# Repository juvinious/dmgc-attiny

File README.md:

# DMGC-ATTINY VIEWER

A software implementation of the ATTINY85 code that [BucketM0use](https://github.com/MouseBiteLabs/) made for the [DMGC](https://github.com/MouseBiteLabs/Game-Boy-DMG-Color).

# HOW TO USE

## Run with SDL2

- Install c++ development tools, libyaml-cpp and SDL2
  - Example in Ubuntu install: apt-get install build-essential libyaml-cpp-dev libsdl2-dev 
- make
- executables are dropped in bin directory

## Examples

There are currently three example sketches

### DMGC-IPS-ATTINY85

This is the original sketch. Refer to [DMGC-IPS-01](https://github.com/MouseBiteLabs/Game-Boy-DMG-Color/tree/main/DMGC-IPS-01#button-leds-and-attiny85) for details.

### DMGC-IPS-ATTINY85-PLUS

This is the same as the original, but improved using the key/button handler which is using states to determine the positions of buttons. Better practice instead of blocking with while loops. :P.

### BREATHING

A more extended example, allowing for different modes.
  - Breathing - Increases and decreases brightness at a specific rate. Changes to random color when brightness is at 5 or below, starting a new cycle
  - Left to Right (LTR) - Run a gradient from left to right while brightning the a random color to the max, fade out and then restart
  - Right to Left - Same as LTR, but going in the opposite direction
  - Center Out - Same as LTR, but starting from right and select and going outward
  - Out to Center - Same as LTR, but starting at up and A
  - Random - Randomizes the order of the cycling as LTR

## Deploy to ATTINY85 in Arduino IDE

- Symlink library directory as src in the directory of the sketch
  - In windows: mklink /J src ..\..\library
  - In linux: ln -s ../../library src
- Open ino sketch, compile & upload

## Finally

Have fun!

# TODO

- Cleanup/Optimize configuration content
- Add additional utils as needed
- Adafruit_NeoPixel
  - Implement other functionality
- EEPROM
  - Fix get/put templating
  - Implement other functionality
- Implement fast_led library functionality (http://fastled.io/)
- Try to match as close as possible the hardware speed at 8mhz

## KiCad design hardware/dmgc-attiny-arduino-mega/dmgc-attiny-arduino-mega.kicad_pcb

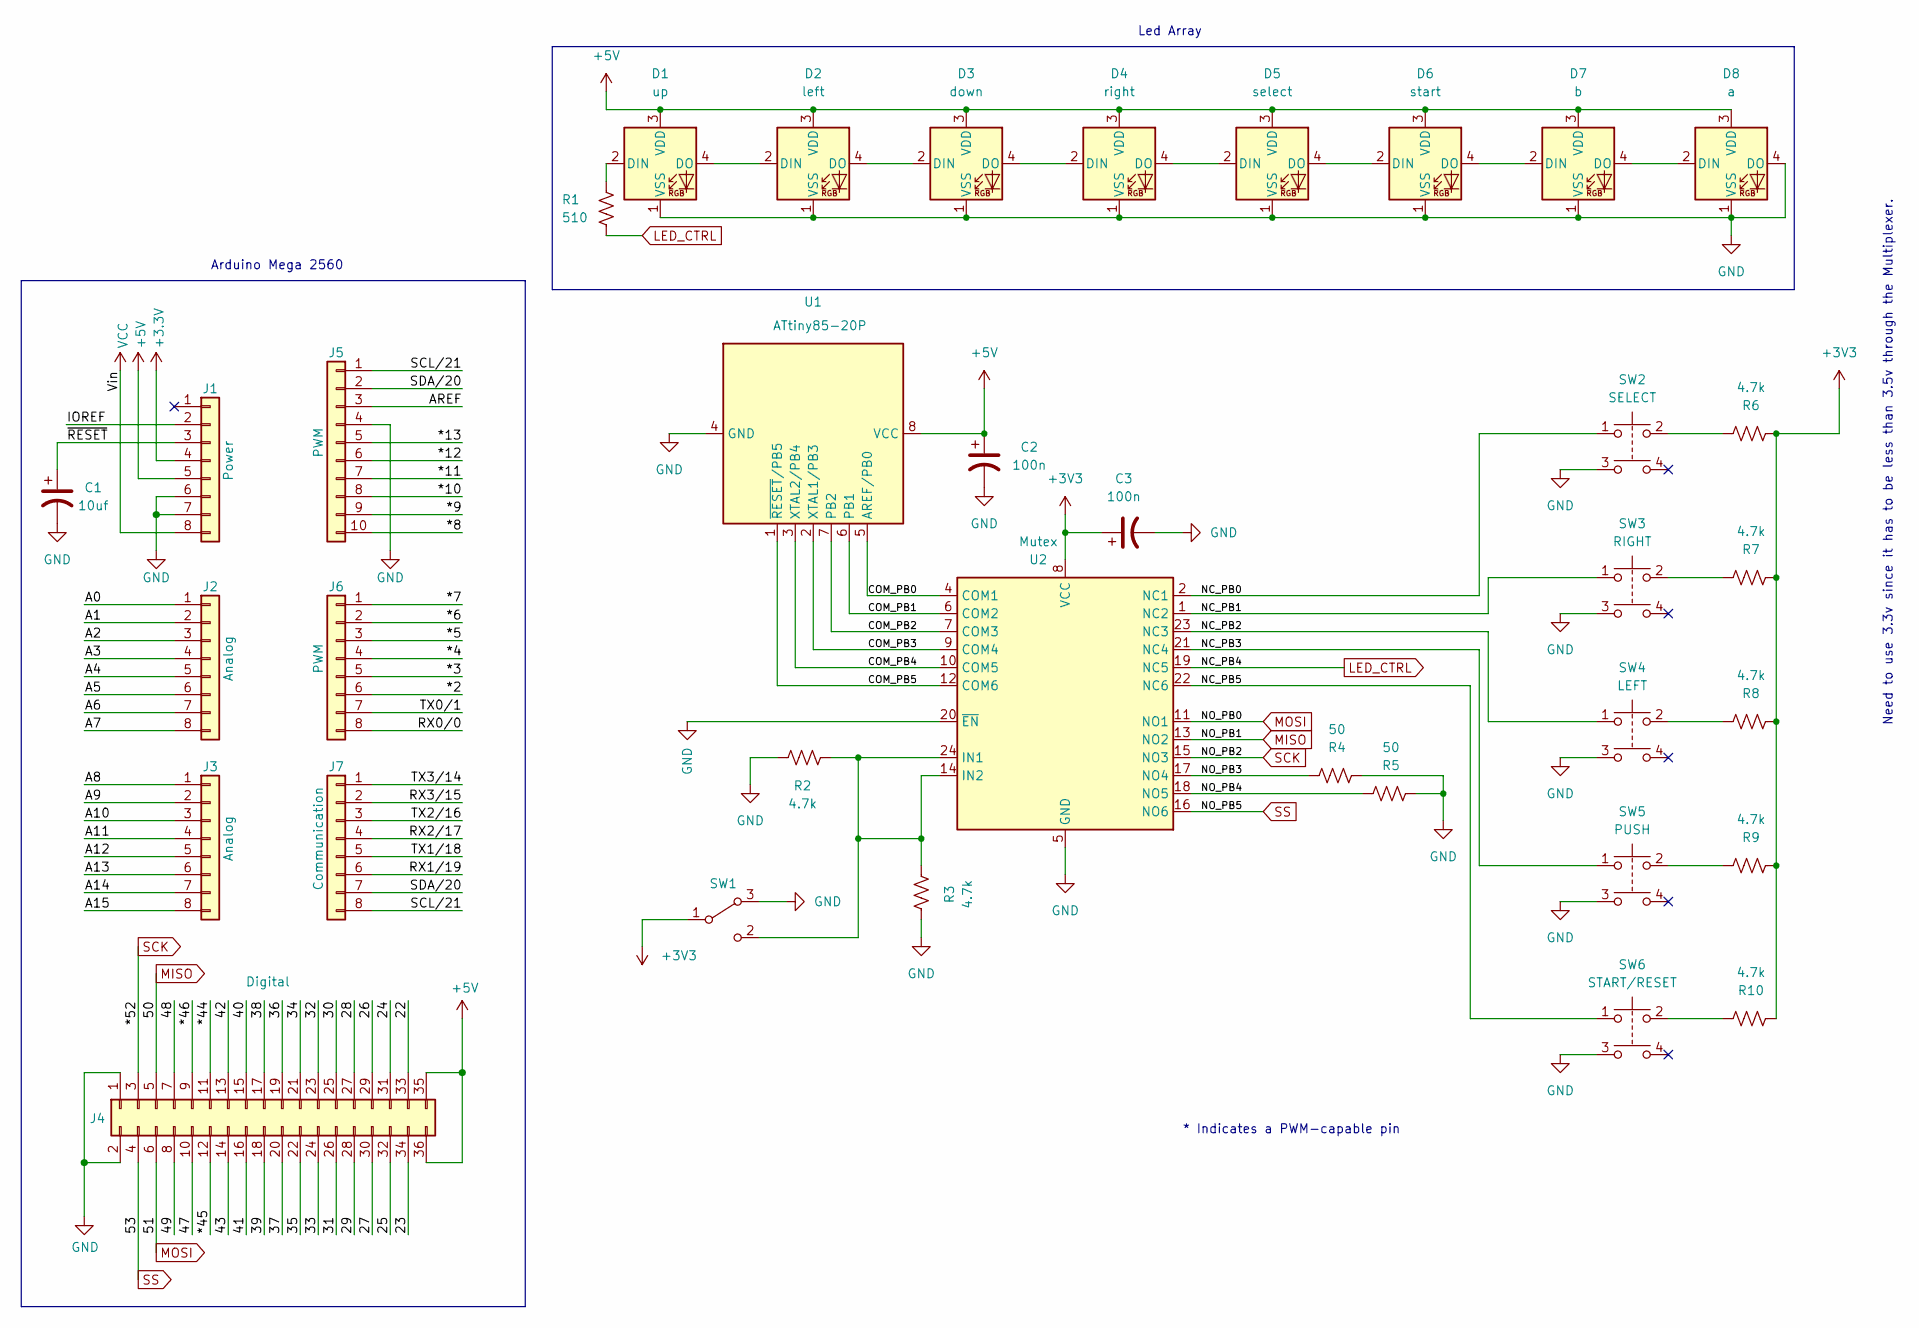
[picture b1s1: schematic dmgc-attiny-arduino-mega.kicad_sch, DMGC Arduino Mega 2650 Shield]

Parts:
C1: 10uf; C_0603_1608Metric
C2, C3: 100n; C_0603_1608Metric
D1: up; LED_Inolux_IN-PI554FCH_PLCC4_5.0x5.0mm_P3.2mm
D2: left; LED_Inolux_IN-PI554FCH_PLCC4_5.0x5.0mm_P3.2mm
D3: down; LED_Inolux_IN-PI554FCH_PLCC4_5.0x5.0mm_P3.2mm
D4: right; LED_Inolux_IN-PI554FCH_PLCC4_5.0x5.0mm_P3.2mm
D5: select; LED_Inolux_IN-PI554FCH_PLCC4_5.0x5.0mm_P3.2mm
D6: start; LED_Inolux_IN-PI554FCH_PLCC4_5.0x5.0mm_P3.2mm
D7: b; LED_Inolux_IN-PI554FCH_PLCC4_5.0x5.0mm_P3.2mm
D8: a; LED_Inolux_IN-PI554FCH_PLCC4_5.0x5.0mm_P3.2mm
J1: Power; PinSocket_1x08_P2.54mm_Vertical
J2, J3: Analog; PinSocket_1x08_P2.54mm_Vertical
J4: Digital; PinSocket_2x18_P2.54mm_Vertical
J5: PWM; PinSocket_1x10_P2.54mm_Vertical
J6: PWM; PinSocket_1x08_P2.54mm_Vertical
J7: Communication; PinSocket_1x08_P2.54mm_Vertical
R1: 510; R_0603_1608Metric
R2, R3, R6, R7, R8, R9, R10: 4.7k; R_0603_1608Metric
R4, R5: 50; R_0603_1608Metric
SW1: Toggle Flash / Run; SW_E-Switch_EG1224_SPDT_Angled
SW2: SELECT; SW_PUSH_6mm
SW3: RIGHT; SW_PUSH_6mm
SW4: LEFT; SW_PUSH_6mm
SW5: PUSH; SW_PUSH_6mm
SW6: START/RESET; SW_PUSH_6mm
U1: ATtiny85-20P; DIP-8_W7.62mm
U2: Mutex; TSSOP-24_4.4x7.8mm_P0.65mm

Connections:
+5V: C2.1, D1.3 (VDD), D2.3 (VDD), D3.3 (VDD), D4.3 (VDD), D5.3 (VDD), D6.3 (VDD), D7.3 (VDD), D8.3 (VDD), J1.5, J4.35, J4.36, U1.8 (VCC)
/22: J4.33
/23: J4.34
/24: J4.31
/25: J4.32
/26: J4.29
/27: J4.30
/28: J4.27
/29: J4.28
/30: J4.25
/31: J4.26
/32: J4.23
/33: J4.24
/34: J4.21
/35: J4.22
/36: J4.19
/37: J4.20
/38: J4.17
/39: J4.18
/40: J4.15
/41: J4.16
/42: J4.13
/43: J4.14
/47: J4.10
/48: J4.7
/49: J4.8
/*2: J6.6
/*3: J6.5
/*4: J6.4
/*5: J6.3
/*6: J6.2
/*7: J6.1
/*8: J5.10
/*9: J5.9
/*10: J5.8
/*11: J5.7
/*12: J5.6
/*13: J5.5
/*44: J4.11
/*45: J4.12
/*46: J4.9
/A0: J2.1
/A1: J2.2
/A2: J2.3
/A3: J2.4
/A4: J2.5
/A5: J2.6
/A6: J2.7
/A7: J2.8
/A8: J3.1
/A9: J3.2
/A10: J3.3
/A11: J3.4
/A12: J3.5
/A13: J3.6
/A14: J3.7
/A15: J3.8
/AREF: J5.3
/COM_PB0: U1.5 (AREF/PB0), U2.4 (COM1)
/COM_PB1: U1.6 (PB1), U2.6 (COM2)
/COM_PB2: U1.7 (PB2), U2.7 (COM3)
/COM_PB3: U1.2 (XTAL1/PB3), U2.9 (COM4)
/COM_PB4: U1.3 (XTAL2/PB4), U2.10 (COM5)
/COM_PB5: U1.1 (~RESET/PB5), U2.12 (COM6)
/IOREF: J1.2
/NC_PB0: SW2.1, U2.2 (NC1)
/NC_PB1: SW3.1, U2.1 (NC2)
/NC_PB2: SW4.1, U2.23 (NC3)
/NC_PB3: SW5.1, U2.21 (NC4)
/NC_PB5: SW6.1, U2.22 (NC6)
/NO_PB3: R4.2, U2.17 (NO4)
/NO_PB4: R5.2, U2.18 (NO5)
/RX0/0: J6.8
/RX1/19: J7.6
/RX2/17: J7.4
/RX3/15: J7.2
/SCL/21: J5.1, J7.8
/SDA/20: J5.2, J7.7
/TX0/1: J6.7
/TX1/18: J7.5
/TX2/16: J7.3
/TX3/14: J7.1
/~RESET: C1.1, J1.3
GND: C1.2, C2.2, C3.2, D1.1 (VSS), D2.1 (VSS), D3.1 (VSS), D4.1 (VSS), D5.1 (VSS), D6.1 (VSS), D7.1 (VSS), D8.1 (VSS), D8.4 (DO), J1.6, J1.7, J4.1, J4.2, J5.4, R2.1, R3.1, R4.1, R5.1, SW1.3 (A), SW2.3, SW3.3, SW4.3, SW5.3, SW6.3, U1.4 (GND), U2.5 (GND), U2.20 (~EN)
LED_CTRL: R1.1, U2.19 (NC5)
MISO: J4.5, U2.13 (NO2)
MOSI: J4.6, U2.11 (NO1)
unnamed: D1.2 (DIN), R1.2
unnamed: D1.4 (DO), D2.2 (DIN)
unnamed: D2.4 (DO), D3.2 (DIN)
unnamed: D3.4 (DO), D4.2 (DIN)
unnamed: D4.4 (DO), D5.2 (DIN)
unnamed: D5.4 (DO), D6.2 (DIN)
unnamed: D6.4 (DO), D7.2 (DIN)
unnamed: D7.4 (DO), D8.2 (DIN)
unnamed: R2.2, R3.2, SW1.2 (C), U2.14 (IN2), U2.24 (IN1)
unnamed: R6.2, SW2.2
unnamed: R7.2, SW3.2
unnamed: R8.2, SW4.2
unnamed: R9.2, SW5.2
unnamed: R10.2, SW6.2
SCK: J4.3, U2.15 (NO3)
SS: J4.4, U2.16 (NO6)
VCC: J1.8

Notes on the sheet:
Need to use 3.3v since it has to be less than 3.5v through the Multiplexer.
Arduino Mega 2560
Led Array
* Indicates a PWM-capable pin

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
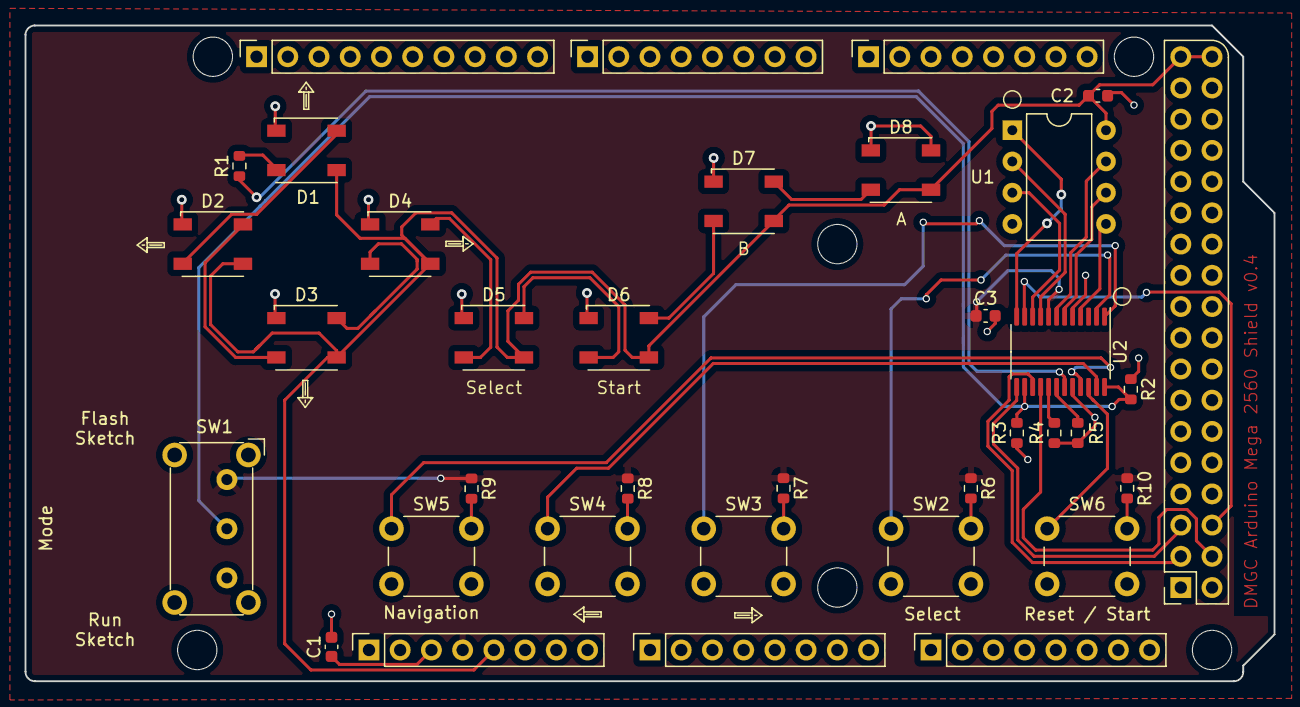
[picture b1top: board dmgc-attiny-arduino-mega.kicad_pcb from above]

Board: 2 copper layers, 101.6 x 53.3 mm, 48 parts (0 on the bottom side), 38 nets.

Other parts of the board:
MH1, MH2, MH3, MH4, MH5, MH6: MountingHole_3.2mm
arrow**: Up; Arrow
arrow**#2, arrow**#4, arrow**#6: Left; Arrow
arrow**#3: Down; Arrow
arrow**#5: Right; Arrow

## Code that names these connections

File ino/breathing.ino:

#include <Adafruit_NeoPixel.h>
#include <EEPROM.h>

// Which pin on the Arduino is connected to the NeoPixels?
#define OUT           PCINT4 // PB4
#define pushbtn       PCINT3 // PB3
#define leftbtn       PCINT2 // PB2
#define rightbtn      PCINT1 // PB1
#define selbtn        PCINT0 // PB0

// Define order of LEDs in string, starting with 0
#define l             1
#define u             0
#define d             2
#define r             3
#define se            4
#define st            5
#define b             6
#define a             7

#define NUMPIXELS 8 // Popular NeoPixel ring size

Adafruit_NeoPixel pixels(NUMPIXELS, OUT, NEO_GRB + NEO_KHZ800);

volatile uint8_t brightness;
volatile uint8_t color_type;
const uint8_t    COLOR_QTY  = 9;
const uint8_t    DEBOUNCE_DELAY = 50;
const uint8_t    BRIGHTNESS_INC = 5;
const uint8_t    MIN_BRIGHTNESS = 5;
const uint8_t    MAX_BRIGHTNESS = 50;

volatile uint8_t brightness_change_flag = 0;

// cycles through different colors:    red  org  ylw  grn  cyan blue purp wht  off
volatile uint8_t red[COLOR_QTY]   =  { 255, 255, 255, 0,   0,   0,   255, 255, 0};
volatile uint8_t green[COLOR_QTY] =  { 0,   100, 200, 255, 255, 0,   0,   255, 0};
volatile uint8_t blue[COLOR_QTY]  =  { 0,   0,   0,   0,   255, 255, 255, 255, 0};

void setup() {

  pixels.begin();

  EEPROM.get(0, brightness);
  EEPROM.get(1, color_type);

  // Check if EPROM data was corrupted, set brightness to max or min values
  if (brightness>MAX_BRIGHTNESS){
    brightness=MAX_BRIGHTNESS;
  }
  if (brightness<MIN_BRIGHTNESS){
    brightness=MIN_BRIGHTNESS;
  }
  
  pixels.setBrightness(brightness);

  // Inputs *MUST NOT* use ATTINY's pull-ups. These will rely on the GBC CPU's internal pull-ups to 3.3V. The ATTINY is powered by 5V!!
  pinMode(pushbtn, INPUT);
  pinMode(leftbtn, INPUT);
  pinMode(rightbtn, INPUT);
  pinMode(selbtn, INPUT);

  // Skip intro if nav switch is pushed in
  if (digitalRead(pushbtn)==HIGH){

      pixels.clear();
      pixels.show();
      delay(1100);

      int y=6;
      int k=0;

      uint8_t introarray[24] = {8,8,8,8,8,8,8,2,2,0,0,6,6,3,3,5,5,5,5,5,5,5,5,5};

      // Loop through values in introarray. Delays were timed experimentally.
      for(int j=0; j<16; j++){
        for(int i=0; i<NUMPIXELS; i++){
          if(i==l){
            k=introarray[j+6];
          }
          if(i==u){
            k=introarray[j+5];
          }
          if(i==d){
            k=introarray[j+5];
          }
          if(i==r){
            k=introarray[j+4];
          }
          if(i==se){
            k=introarray[j+3];
          }
          if(i==st){
            k=introarray[j+2];
          }
          if(i==b){
            k=introarray[j+1];
          }
          if(i==a){
            k=introarray[j];
          }
        pixels.setPixelColor(i, pixels.Color(red[k],green[k],blue[k]));
        pixels.show();
        delay(y);
        }
      }
      delay(2000);
  }else{
    while(1){};
  }
//  while(!digitalRead(pushbtn)){
//    delay(10);
//  }
}

void loop() {
  // Update LED outputs
  outputLED(color_type);

  // If nav switch is pressed
  if(digitalRead(pushbtn)==LOW){
    // Pause the program to debounce the switch, check to make sure it's still pressed
    delay(DEBOUNCE_DELAY);
    if(digitalRead(pushbtn)==LOW){

      // I'm sorry, I forgot to comment this, and now I'm reading it months later
      while(!digitalRead(pushbtn) && !digitalRead(pushbtn)){
        if(digitalRead(rightbtn)==LOW){
        delay(DEBOUNCE_DELAY);
          if(digitalRead(rightbtn)==LOW){
            while(!digitalRead(rightbtn)){
              delay(DEBOUNCE_DELAY);
            }
            if(brightness+BRIGHTNESS_INC>MAX_BRIGHTNESS){
              brightness=MAX_BRIGHTNESS;
            }else{
              brightness=brightness+BRIGHTNESS_INC;
            }
            brightness_change_flag = 1;
            pixels.setBrightness(brightness);
            outputLED(color_type);
          }
        }
        
        if(digitalRead(leftbtn)==LOW){
          delay(DEBOUNCE_DELAY);
          if(digitalRead(leftbtn)==LOW){
            while(!digitalRead(leftbtn) && !digitalRead(pushbtn)){
              delay(DEBOUNCE_DELAY);
            }
            if(brightness-BRIGHTNESS_INC<MIN_BRIGHTNESS){
              brightness=MIN_BRIGHTNESS;
            }else{
              brightness=brightness-BRIGHTNESS_INC;
            }
            brightness_change_flag = 1;
            pixels.setBrightness(brightness);
            outputLED(color_type);
          }
        }
        delay(DEBOUNCE_DELAY);
      }
      
      if(brightness_change_flag==0){
        if(color_type==COLOR_QTY-1){
          color_type=0;
        }else{
          color_type = color_type+1;
        }
      }
      // Save brightness and color setting to EPROM
      EEPROM.put(0,brightness);
      EEPROM.put(1,color_type);
      brightness_change_flag = 0;
      }
    }
  }

void outputLED(uint8_t x){
  for(int i=0; i<NUMPIXELS; i++) { // For each pixel...
    pixels.setPixelColor(i, pixels.Color(red[x],green[x],blue[x]));
    pixels.show();   // Send the updated pixel colors to the hardware.
  }  
}

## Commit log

2022-09-29 First commit.
2022-09-29 Cleaned up directory.
2022-10-02 Getting compilation closer.
2022-10-02 Fixed compilation.
2022-10-02 Updated readme.
2022-10-02 Added yaml support. Updated configuration.
2022-10-03 Moved configuration over to its own file. Added ttf font.
2022-10-04 Begin creating leds and placement information.
2022-10-05 Begin setting color and showing content.
2022-10-05 Begin adding background.
2022-10-05 Set placement of leds and descriptions. Start handling keys.
2022-10-06 Removed unecessary header. Added keymapping.
2022-10-07 Cleanup code. Add key and font handlers.
2022-10-08 Fix brightness. Organize files and add new project ino.
2022-10-09 Begin working on compiling in arduino ide.
2022-10-10 Moved button handler to arduino util library.
2022-10-11 Fixes for arduino ide.
2022-10-11 Added EPROM support.
2022-10-11 Cleanup new examples. Added intro to DMGC_UTILS.
2022-10-11 Improve breathing example.
2022-10-11 Modify rgb value on each iteration.
2022-10-12 Randomize seed. Begin adding modes for breathing example.
2022-10-12 Initialize button linked list next to null, in order to avoid garbage.
2022-10-12 Cleanup breathing example.
2022-10-12 Update README.
2022-10-12 Updated breathing second mode.
2022-10-13 Complete breathing example.
2022-10-13 Cleanup breathing and add saving to EEPROM.
2022-10-13 Image typo.
2022-10-13 Image fix.
2022-10-13 Embed image of breathing example
2022-10-17 Added kicad files for arduino shield.
2022-10-18 Fixed increment bug, which was causing a jump directly to target number.
2022-10-19 Updated arduino shield, start implementing a multiplexer to switch from flashing the attiny85 to running the attiny85.
2022-10-20 Updated arduino shield to include switching circuit for flashing and running.
2022-10-21 Updated arduino shield routing and fixed pcb issues.
2022-10-21 Updated readme TODO.
2022-10-22 Begin fixing color pallete changing and fading between contexts.
2022-10-22 Begin cleaning up pixel handling.
2022-10-22 Cleaned up pixel handling. Simplified state handling and re-implemented all modes.
2022-10-26 Implemented simple list. Fixed random mode.
2022-10-26 Improve dmgc startup animation speed.
2022-10-28 Begin building out configuration mechanism of modes and colors.
2022-10-30 Updated gerbers to v0.3, fixed 0603 footprints.
2022-11-05 Updated gerbers to v0.4, fixed switch problem with pins reversed. Moved C2 to a better location. Added labels for switch.
2022-11-12 Added some fixes and debounce the hardware buttons.
